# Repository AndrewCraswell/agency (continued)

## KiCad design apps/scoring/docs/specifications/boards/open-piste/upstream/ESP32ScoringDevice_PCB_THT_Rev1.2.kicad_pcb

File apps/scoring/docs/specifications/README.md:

# Scoring specifications

This directory separates normative and project specification inputs from implementation notes and public prior art.

## Rules and protocol sources

| Document | Role | Source and integrity |
| --- | --- | --- |
| [`fie-rules-for-competitions-introduction-2017-en.pdf`](fie-rules-for-competitions-introduction-2017-en.pdf) | Official introduction and historical basis for the FIE Rules for Competitions | [FIE rules index](https://fie.org/documents/rules), [official PDF](https://static.fie.org/uploads/28/141005-RIntroduction%20ang.pdf), SHA-256 `AA73C641A31101F7B3159B84717583DB9B40537E49DB04A675704B5786669916` |
| [`fie-organisation-rules-2026-08-en.pdf`](fie-organisation-rules-2026-08-en.pdf) | Normative FIE Organisation Rules, Book 2, August 2026 | [FIE rules index](https://fie.org/documents/rules), [official PDF](https://static.fie.org/uploads/40/204283-Organisation%20rules%20August%202026%20ang.pdf), SHA-256 `5CAC44B8D1A7FD2C8AE1FB65DA5B52C0F33E63F9718FD9696460865227A93BB1` |
| [`fie-material-rules-2026-08-en.pdf`](fie-material-rules-2026-08-en.pdf) | Normative FIE Material Rules, Book 3, August 2026 | [FIE rules index](https://fie.org/documents/rules), [official PDF](https://static.fie.org/uploads/40/204157-book%20material%20August%202026%20ang.pdf), SHA-256 `1489D28ED6F3C91E27ECDF75BB29B4ED65C688A012F544D37D946A9DA81AFC26` |
| [`fie-technical-rules-2026-08-en.pdf`](fie-technical-rules-2026-08-en.pdf) | Normative FIE Technical Rules, Book 1, August 2026 | [FIE rules index](https://fie.org/documents/rules), [official PDF](https://static.fie.org/uploads/40/204138-Technical%20rules%20August%202026%20ang.pdf), SHA-256 `852D636402DCCB7BBD107C346261430A1B1977AB0FE9C2A2AE663AF52B5BD880` |
| [`fie-traceability-matrix.md`](fie-traceability-matrix.md) | Local article-to-requirement decomposition | Derived from the pinned August 2026 FIE PDF; the PDF remains authoritative |
| [`protocols/cyrano-protocol-1.0-2008-12-05.pdf`](protocols/cyrano-protocol-1.0-2008-12-05.pdf) | Historical EFP1/Cyrano 1.0 provenance only; not a product implementation target | [Public Ophardt mirror](https://docs.ophardt.online/images/9/96/Cyrano_1.0.pdf), SHA-256 `ACBCF1CBF857429CF9FA64558E3B1C3EEDC9ACF1F891177E8471C1938B663828` |
| [`protocols/cyrano-protocol-1.1-2019-10-11.pdf`](protocols/cyrano-protocol-1.1-2019-10-11.pdf) | EFP1.1/Cyrano 1.1 protocol, adding P-card and centisecond fields | [Public protocol mirror](https://superfencingsystem.com/CyranoProtocol-1-1.pdf), SHA-256 `D422342D83072C8EC38DB6E0403C741ED6A82A08095510AFD499568E26C5C0C3` |
| [`protocols/rs422-fpa-protocol-3.04a-2019-05-21.pdf`](protocols/rs422-fpa-protocol-3.04a-2019-05-21.pdf) | Latest publicly located Fencing Piste Apparatus RS422 output protocol; covers the electrical layer, messages 1-9, refresh scheduling, and receiver validation | [Super Fencing System protocol mirror](https://superfencingsystem.com/RS422-FPA-V3.04a.pdf), SHA-256 `E76B97A2B701D83323F22B9A7C42C3D053ED4FF0DF7163BCB1AB43EE97B50A91` |
| [`protocols/fencing-time-scoring-machine-integration-guide.pdf`](protocols/fencing-time-scoring-machine-integration-guide.pdf) | Fencing Time 4.6 vendor integration guide, August 2024; covers Cyrano 1.0/1.1 setup, bout exchange, Fencing Time Live, data forwarding, and StripView | [Fencing Time PDF](https://fencingtime.s3.amazonaws.com/FencingTimeScoringMachineIntegrationGuide.pdf), SHA-256 `494532474DBF541F6019D6C36D507E1CE81E4D274D780D622515A27F2223D255` |
| [`protocols/fie-fencing-radio-specifications-rev2.0.pdf`](protocols/fie-fencing-radio-specifications-rev2.0.pdf) | FIE basic radio specification for a separate wireless clock Start/Stop system; requires two remotes, selectable sub-GHz frequencies, acknowledgement, monitoring, encryption, and less-than-100-ms latency | [Official FIE PDF](https://static.fie.org/uploads/8/44449-Fencing%20Radio%20specifications%20Rev2.0.pdf), SHA-256 `1C4E1F3BB9C1F491E4C3ABCC0AD39F7423FC8DDDA1E734FD0C9F65EE6DF44E4A` |

The Cyrano PDFs identify their protocol authors and FIE/manufacturer working-group history, but the files above were
retrieved from public mirrors because a current FIE-hosted protocol download was not located. Preserve their hashes and
treat any implementation ambiguity as unresolved until it is checked against interoperable apparatus and tournament
software.

The proposed product implements EFP1.1 only. It does not advertise, negotiate, or fall back to Cyrano 1.0/EFP1. The
older PDF is retained solely as historical protocol provenance.

The FIE radio document describes a minimal 810-960 MHz Start/Stop clock system with main and backup remotes. It does
not describe the full-function infrared handhelds supplied with the commercial apparatus reviewed here. The proposed
product therefore keeps encrypted IR as its primary referee remote and treats a separate FIE radio subsystem as a
homologation clarification with SEMI, not as a baseline product claim.

The current Super Fencing System protocol index still identifies RS422-FPA 3.04a as its FPA specification, and no
newer public revision was located on August 24, 2026. The pinned PDF is a public community-protocol mirror, not evidence
that this project is FIE-homologated or certified interoperable. Recheck the source index and test against target
apparatus and receivers before freezing a production implementation.

## Integration evidence

The Fencing Time guide is vendor documentation for configuring a supported scoring machine with Fencing Time Scoring
Device Manager. It is evidence for Fencing Time's expected network configuration and workflow, but the Cyrano PDFs above
remain the message-level protocol inputs. Compatibility still requires an interoperability test against the current
Fencing Time release; the guide does not make this project's implementation certified or supported by Fencing Time.

Super Fencing System publishes a [current protocol and machine compatibility table](https://superfencingsystem.com/protocols.html)
and advertises native Cyrano UDP support on its [product page](https://superfencingsystem.com/). No separate general
Super Fencing System app-integration manual was located on August 24, 2026. Its downloadable manuals describe the
SFS-Link hardware adapters for Favero serial or RS422-FPA sources, not native Cyrano integration. For native Ethernet
integration, use the pinned Cyrano 1.1 PDF above as the implementation input and treat successful operation with the
current Super Fencing System app as a separate test gate.

## Product specification

[`proposed-product-specification.md`](proposed-product-specification.md) defines the proposed commercial product,
feature priorities, hardware and power architecture, inputs and outputs, scoring authority, protocol directions,
remote controls, firmware responsibilities, recovery, faults, and minimum conformance work. It is a product proposal,
not a schematic release or homologation claim.

[`weapon-scoring-programming-specification.md`](weapon-scoring-programming-specification.md) consolidates the required
foil, epee, and sabre state-machine behavior. Normative FIE requirements, released project decisions, and prior-art
observations remain explicitly distinguished.

[`scoring-calculation-implementation-guide.md`](scoring-calculation-implementation-guide.md) translates that baseline
into code-facing definitions and exact calculations for candidates, qualification, resistance uncertainty, foil
classification, epee double touches, weapon lockout, sabre whip-over, diagnostics, and output latching. Each weapon table
identifies whether behavior comes from FIE or a deterministic project selection and links to pinned prior-art code
blocks. Its appendices provide implementation pseudocode without copying the cited repositories.

## Commercial manuals and feature baseline

The [`manuals`](manuals/) directory preserves the official Favero apparatus/repeater documents, the Virtual Scoring
Machine program manual, and the Skewered Fencing manual snapshot used for product comparison. Its manifest records
source URLs, page counts, hashes, and the important distinction between Skewered's native HTML manual and its separate
PDF quick-start guide.

[`commercial-scoring-machine-feature-catalog.md`](commercial-scoring-machine-feature-catalog.md) assigns stable feature
IDs to the documented weapon modes, bout workflow, diagnostics, remotes, protocols, repeaters, update paths, power, and
mechanical capabilities. These are competitive/product inputs; they become project requirements only through an
explicit decision and never override the FIE rules.

## Prior art

The [`prior-art`](prior-art/) directory contains the commit-pinned GitHub repository catalog and its comparison against
the FIE-derived requirements. The
[`open-source-commercial-feature-gap-analysis.md`](prior-art/open-source-commercial-feature-gap-analysis.md) also maps
the retained competitive public references to the commercial feature IDs and prioritizes missing scoring, workflow,
interoperability, diagnostics, and recovery evidence. Public code is evidence of earlier implementation approaches, not
a normative authority.

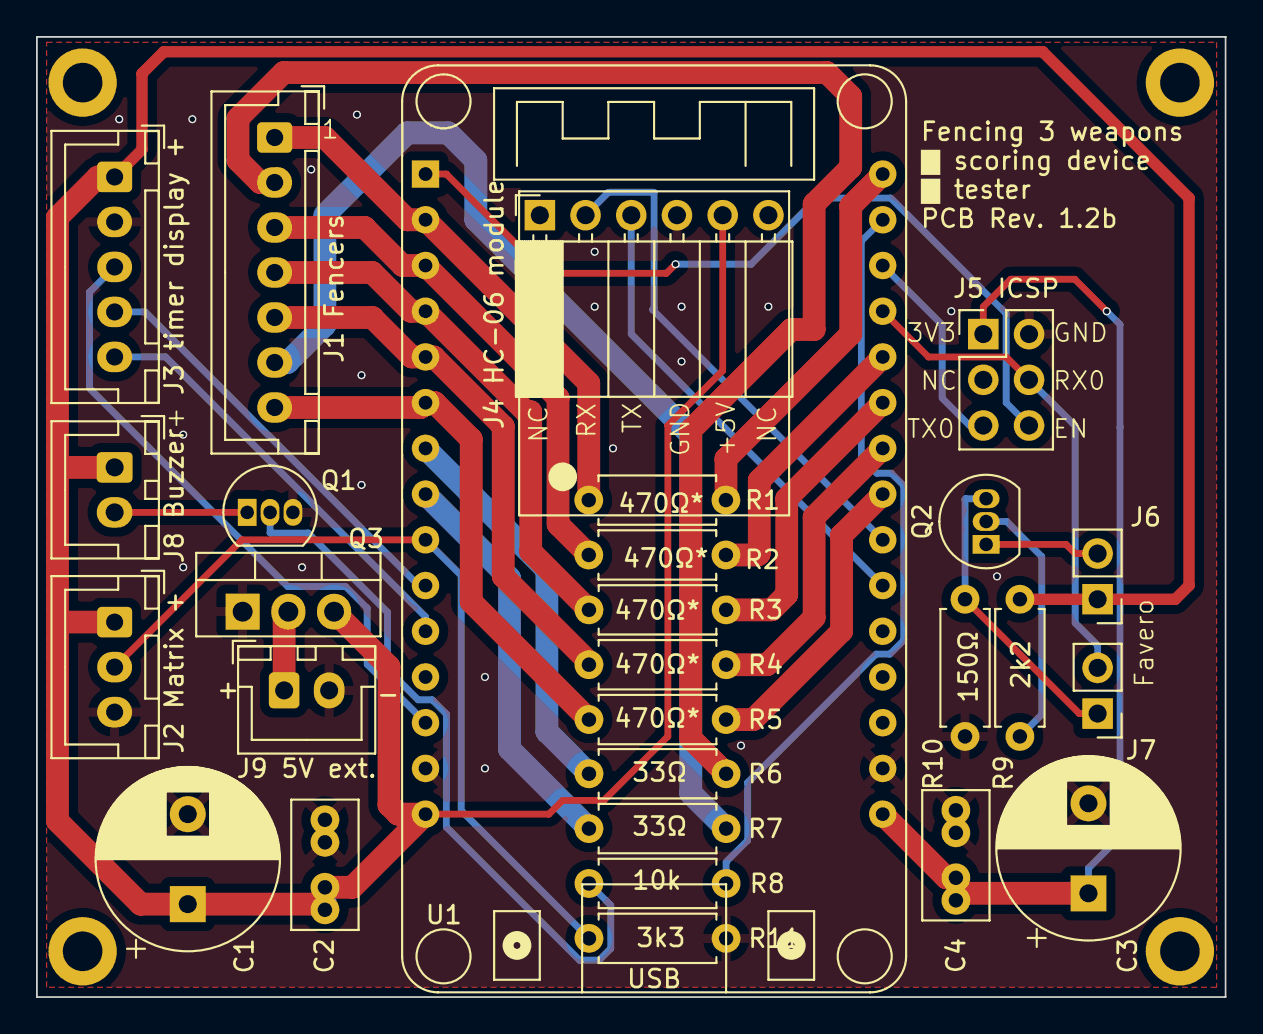
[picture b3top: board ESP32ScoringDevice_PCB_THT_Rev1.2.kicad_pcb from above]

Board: 2 copper layers, 66.0 x 53.3 mm, 32 parts (0 on the bottom side), 33 nets.

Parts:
C1, C3: 470µF; CP_Radial_D10.0mm_P5.00mm
C2, C4: 100nF; C_Rect_L7.0mm_W3.5mm_P2.50mm_P5.00mm
H1, H2, H3, H4: MountingHole_2.2mm_M2_DIN965_Pad
J1 Fencers: Fencers; JST_XH_B7B-XH-A_1x07_P2.50mm_Vertical
J2 Matrix +: WS2812B LED Matrix; JST_XH_B3B-XH-A_1x03_P2.50mm_Vertical
J3 timer display +: MAX7219 Timer Display; JST_XH_B5B-XH-A_1x05_P2.50mm_Vertical
J4 HC-06 module: HC-06 BT module; PinSocket_1x06_P2.54mm_Horizontal
J5 ICSP: ICSP; PinHeader_2x03_P2.54mm_Vertical
J6, J7: Conn_01x02; PinHeader_1x02_P2.54mm_Vertical
J8 Buzzer: Buzzer; JST_XH_B2B-XH-A_1x02_P2.50mm_Vertical
J9 5V ext.: 5V ext. Power; JST_XH_B2B-XH-A_1x02_P2.50mm_Vertical
Q1, Q2: BC337; TO-92_Inline
Q3: FQP27P06; TO-220-3_Vertical
R1, R2, R3, R4, R5: 470Ω; R_Axial_DIN0207_L6.3mm_D2.5mm_P7.62mm_Horizontal
R6, R7: 33Ω; R_Axial_DIN0207_L6.3mm_D2.5mm_P7.62mm_Horizontal
R8: 3k3; R_Axial_DIN0207_L6.3mm_D2.5mm_P7.62mm_Horizontal
R9: 2k2; R_Axial_DIN0207_L6.3mm_D2.5mm_P7.62mm_Horizontal
R10: 150Ω; R_Axial_DIN0207_L6.3mm_D2.5mm_P7.62mm_Horizontal
R11: 10k; R_Axial_DIN0207_L6.3mm_D2.5mm_P7.62mm_Horizontal
U1: ESP32_DevKit_V1_DOIT 30pin; esp32_devkit_v1_doit

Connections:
+3.3V: C3.1, C4.1, J5 ICSP.1, U1.16 (3V3)
+5V: C1.1, C2.1, J2 Matrix +.1, J3 timer display +.1, J4 HC-06 module.5, J6.1, J8 Buzzer.1, Q3.3 (S), R9.2, U1.15 (VIN)
GND: C1.2, C2.2, C3.2, C4.2, J2 Matrix +.3, J3 timer display +.2, J4 HC-06 module.4, J5 ICSP.2, J9 5V ext..2, Q1.3 (E), Q3.1 (G), R10.2, R11.2, U1.14 (GND), U1.17 (GND)
unnamed: J1 Fencers.1, R1.2, U1.2 (SENSOR_VP)
unnamed: J1 Fencers.2, R6.2
unnamed: J1 Fencers.3, R2.1, U1.3 (SENSOR_VN)
unnamed: J1 Fencers.4, R3.2, U1.4 (IO34)
unnamed: J1 Fencers.5, R4.2, U1.5 (IO35)
unnamed: J1 Fencers.6, R7.2
unnamed: J1 Fencers.7, R5.2, U1.6 (IO32)
unnamed: J2 Matrix +.2, R11.1, U1.9 (IO26)
unnamed: J3 timer display +.3, U1.13 (IO13)
unnamed: J3 timer display +.4, U1.10 (IO27)
unnamed: J3 timer display +.5, U1.11 (IO14)
unnamed: J4 HC-06 module.2, U1.22 (IO17)
unnamed: J4 HC-06 module.3, U1.21 (IO16)
unnamed: J5 ICSP.4, J7.2, U1.27 (RXD0/IO3)
unnamed: J5 ICSP.5, U1.28 (TXD0/IO1)
unnamed: J5 ICSP.6, U1.1 (EN)
unnamed: J6.2, Q2.1 (C)
unnamed: J7.1, Q2.3 (E), R10.1
unnamed: J8 Buzzer.2, Q1.1 (C)
unnamed: J9 5V ext..1, Q3.2 (D)
unnamed: Q1.2 (B), R8.1
unnamed: Q2.2 (B), R9.1
unnamed: R5.1, U1.23 (IO5)
unnamed: R4.1, U1.24 (IO18)
unnamed: R3.1, U1.25 (IO19)
unnamed: R2.2, U1.26 (IO21)
unnamed: R8.2, U1.29 (IO22)
unnamed: R1.1, U1.30 (IO23)
unnamed: R7.1, U1.8 (IO25)
unnamed: R6.1, U1.7 (IO33)
